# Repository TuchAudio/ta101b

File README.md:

# TuchAudio 101b
Discrete Phono preamp -- reedition of my very first phono preamp, circa 1987...

## Purpose
Fully symmetrical discrete op-amp phono preamp -- loosely inspirated by _Elektor_ designs. RIAA correction is achieved thru two different ways: low frequency boost is implemented on the feedback network, while the high-frequency rollof is done with a **passive low-pass filter**, for improved signal-to-noise ratio.

## Design quirks
The preamp itself is **fully DC-coupled**, for optimum bass performance; however, that means that the _input stage offset_ is **multiplied** by the low-frecuency gain (+34 dB), which may result on stage saturation. To compensate for that, each channel provides room for `R+` or `R-` resistors, connecting the inverting input (feedback) to the power rails, in case some manual adjustment is needed.

Just like the original build, a **subsonic filter** is integrated into the board. This is a **fourth-order high pass filter** (24 dB/oct) with a cutoff frequency of **11.8 Hz**; again, based on an _Elektor_ design (_Summer Circuits 1984_). However, since it is located _after_ the amplification, the high gain of the stage at low frequencies might saturate the preamp itself, in extreme cases.

DIN and RCA jacks are provided for signal input. Since the _native_ input impedance, being a symmetric op-amp design, is expected to be **extremely high**, space for suitable load (`Rx` and `Cx`) is provided for perfect adaptation; but for added flexibility, it is possible to use the free input for a suitable RC combo in parallel, to match the appropriate cartridge load.

Both direct and subsonic-filtered outputs are provided, and properly selected thru the [509 Input Selector board](../../../ta509). An aditional RCA **output** jack can be installed in order to use the circuit as a _stand-alone preamp_.

### Suggested mods

#### Subsonic output
As previously mentioned, both direct and subsonic outputs are provided, and selected thru the _509 Input Selector Board_; in case a non-selecting board is used (like the [501 Input Selector board](../../../ta501)), you can break the `JP1` and `JP2` jumpers to route the _subsonic_ output to the bus-style/RCA jack output instead (with suitable external bodge wires).

#### DC-block
While being fully DC-coupled is definitely desirable from a sound quality standpoint, it may be troublesome in some extreme cases, especially with _warped_ records. If this is a concern, adding a suitable _capacitor_ (**~100 µF**) in the feedback loop will prevent this. Just lift one pin of `R9/R109` and bodge the capacitor _in series_. **There is no need to use `R+/R-`** in that case, and you should remove them in order to check the _offset polarity_; mount the extra capacitor consequently.

## Specs

- **Power Supply:** +/- 9 V (symmetrical), just a few mA.
- **Gain at 1 kHz:** x50 (+34 dB)
- **Input sensitivity:** 3.6 mV (for 180 mV output)
- **Input impedance:** determined by `Rx/Cx`, either internal or external.
- **Output level and impedance:** 180 mV / 1 KΩ
- **Overload margin:** at least +15 dB
- **Signal-to-noise ratio:** more than 80 dB (estimated)
- **Distortion:** TBD

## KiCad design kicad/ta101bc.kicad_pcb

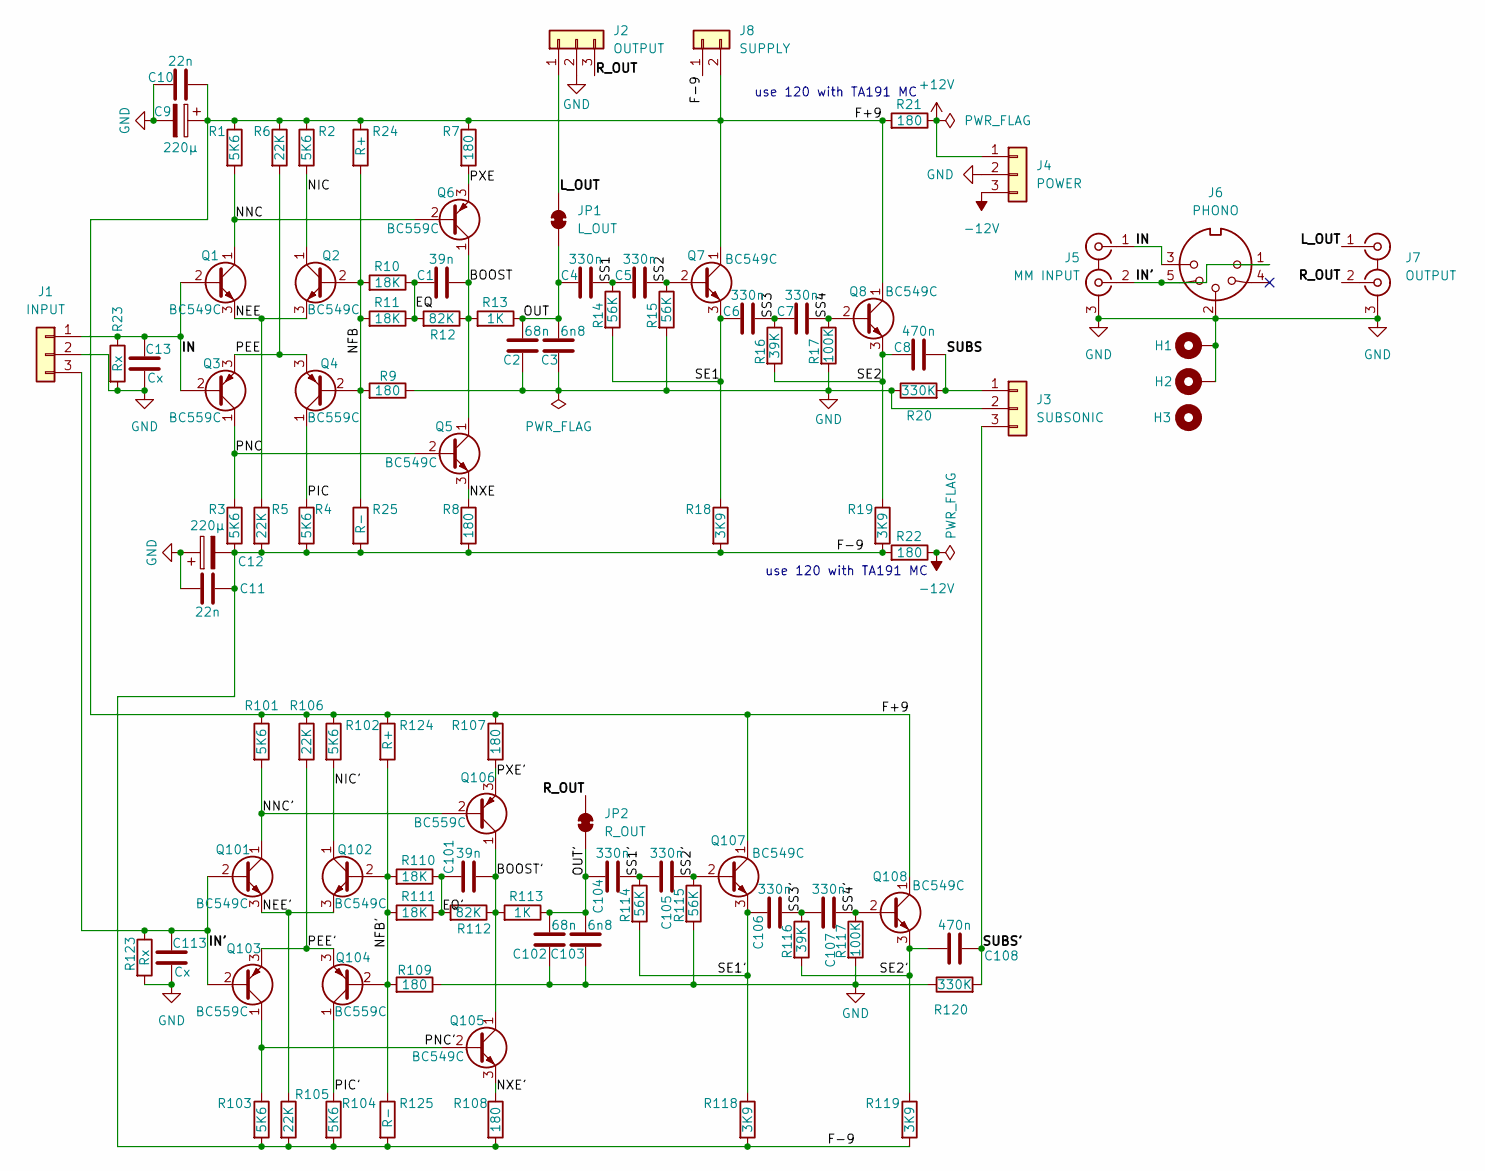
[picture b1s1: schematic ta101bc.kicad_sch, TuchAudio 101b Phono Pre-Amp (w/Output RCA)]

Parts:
C1, C101: 39n; C_Rect_L7.2mm_W3.0mm_P5.00mm_FKS2_FKP2_MKS2_MKP2
C2, C102: 68n; C_Rect_L7.2mm_W3.0mm_P5.00mm_FKS2_FKP2_MKS2_MKP2
C3, C103: 6n8; C_Rect_L7.2mm_W3.0mm_P5.00mm_FKS2_FKP2_MKS2_MKP2
C4, C5, C6, C7, C104, C105, C106, C107: 330n; C_Rect_L7.2mm_W3.0mm_P5.00mm_FKS2_FKP2_MKS2_MKP2
C8, C108: 470n; C_Rect_L7.2mm_W3.0mm_P5.00mm_FKS2_FKP2_MKS2_MKP2
C9, C12: 220µ; CP_Radial_D6.3mm_P2.50mm
C10, C11: 22n; C_Disc_D6.0mm_W2.5mm_P5.00mm
C13, C113: Cx; PinSocket_1x02_P2.54mm_Vertical
H1, H2: MountingHole_Pad; MountingHole_3.2mm_M3_DIN965_Pad
H3: MountingHole; MountingHole_3.2mm_M3_DIN965
J1: INPUT; PinHeader_1x03_P2.54mm_Vertical
J2: OUTPUT; PinHeader_1x03_P2.54mm_Vertical
J3: SUBSONIC; PinHeader_1x03_P2.54mm_Vertical
J4: POWER; PinHeader_1x03_P2.54mm_Vertical
J5: MM INPUT; 2xRCA_vertical
J6: PHONO; DIN 5-180deg
J7: OUTPUT; 2xRCA_vertical
J8: SUPPLY; PinHeader_1x02_P2.54mm_Vertical
JP1: L_OUT; SolderJumper-2_P1.3mm_Bridged2Bar_RoundedPad1.0x1.5mm
JP2: R_OUT; SolderJumper-2_P1.3mm_Bridged2Bar_RoundedPad1.0x1.5mm
Q1, Q2, Q5, Q7, Q8, Q101, Q102, Q105, Q107, Q108: BC549C; TO-92_Inline
Q3, Q4, Q6, Q103, Q104, Q106: BC559C; TO-92_Inline
R1, R2, R3, R4, R101, R102, R103, R104: 5K6; R_Axial_DIN0207_L6.3mm_D2.5mm_P10.16mm_Horizontal
R5, R6, R105, R106: 22K; R_Axial_DIN0207_L6.3mm_D2.5mm_P10.16mm_Horizontal
R7, R8, R9, R21, R22, R107, R108, R109: 180; R_Axial_DIN0207_L6.3mm_D2.5mm_P10.16mm_Horizontal
R10, R11, R110, R111: 18K; R_Axial_DIN0207_L6.3mm_D2.5mm_P10.16mm_Horizontal
R12, R112: 82K; R_Axial_DIN0207_L6.3mm_D2.5mm_P10.16mm_Horizontal
R13, R113: 1K; R_Axial_DIN0207_L6.3mm_D2.5mm_P10.16mm_Horizontal
R14, R15, R114, R115: 56K; R_Axial_DIN0207_L6.3mm_D2.5mm_P10.16mm_Horizontal
R16, R116: 39K; R_Axial_DIN0207_L6.3mm_D2.5mm_P10.16mm_Horizontal
R17, R117: 100K; R_Axial_DIN0207_L6.3mm_D2.5mm_P10.16mm_Horizontal
R18, R19, R118, R119: 3K9; R_Axial_DIN0207_L6.3mm_D2.5mm_P10.16mm_Horizontal
R20, R120: 330K; R_Axial_DIN0207_L6.3mm_D2.5mm_P10.16mm_Horizontal
R23, R123: Rx; PinSocket_1x02_P2.54mm_Vertical
R24, R124: R+; PinSocket_1x02_P2.54mm_Vertical
R25, R125: R-; PinSocket_1x02_P2.54mm_Vertical

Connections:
+12V: J4.1, R21.1
-12V: J4.3, R22.1
/BOOST: C1.2, Q5.1 (C), Q6.1 (C), R12.1, R13.2
/BOOST': C101.2, Q105.1 (C), Q106.1 (C), R112.1, R113.2
/EQ: C1.1, R10.1, R11.1, R12.2
/EQ': C101.1, R110.1, R111.1, R112.2
/F+9: C9.1, C10.2, J8.2, Q7.1 (C), Q8.1 (C), Q107.1 (C), Q108.1 (C), R1.1, R2.1, R6.1, R7.1, R21.2, R24.1, R101.1, R102.1, R106.1, R107.1, R124.1
/F-9: C11.2, C12.2, J8.1, R3.2, R4.2, R5.2, R8.2, R18.2, R19.2, R22.2, R25.2, R103.2, R104.2, R105.2, R108.2, R118.2, R119.2, R125.2
/IN: C13.1, J1.1, J5.1 (IN1), J6.3, Q1.2 (B), Q3.2 (B), R23.1
/IN': C113.1, J1.3, J5.2 (IN2), J6.1, J6.5, Q101.2 (B), Q103.2 (B), R123.1
/L_OUT: J2.1, J7.1 (IN1), JP1.2 (B)
/NEE: Q1.3 (E), Q2.3 (E), R5.1
/NEE': Q101.3 (E), Q102.3 (E), R105.1
/NFB: Q2.2 (B), Q4.2 (B), R9.2, R10.2, R11.2, R24.2, R25.1
/NFB': Q102.2 (B), Q104.2 (B), R109.2, R110.2, R111.2, R124.2, R125.1
/NIC: Q2.1 (C), R2.2
/NIC': Q102.1 (C), R102.2
/NNC: Q1.1 (C), Q6.2 (B), R1.2
/NNC': Q101.1 (C), Q106.2 (B), R101.2
/NXE: Q5.3 (E), R8.1
/NXE': Q105.3 (E), R108.1
/OUT: C2.1, C3.1, C4.1, JP1.1 (A), R13.1
/OUT': C102.1, C103.1, C104.1, JP2.1 (A), R113.1
/PEE: Q3.3 (E), Q4.3 (E), R6.2
/PEE': Q103.3 (E), Q104.3 (E), R106.2
/PIC: Q4.1 (C), R4.1
/PIC': Q104.1 (C), R104.1
/PNC: Q3.1 (C), Q5.2 (B), R3.1
/PNC': Q103.1 (C), Q105.2 (B), R103.1
/PXE: Q6.3 (E), R7.2
/PXE': Q106.3 (E), R107.2
/R_OUT: J2.3, J7.2 (IN2), JP2.2 (B)
/SE1: C6.1, Q7.3 (E), R14.2, R18.1
/SE1': C106.1, Q107.3 (E), R114.2, R118.1
/SE2: C8.1, Q8.3 (E), R16.2, R19.1
/SE2': C108.1, Q108.3 (E), R116.2, R119.1
/SS1: C4.2, C5.1, R14.1
/SS1': C104.2, C105.1, R114.1
/SS2: C5.2, Q7.2 (B), R15.1
/SS2': C105.2, Q107.2 (B), R115.1
/SS3: C6.2, C7.1, R16.1
/SS3': C106.2, C107.1, R116.1
/SS4: C7.2, Q8.2 (B), R17.1
/SS4': C107.2, Q108.2 (B), R117.1
/SUBS: C8.2, J3.1, R20.2
/SUBS': C108.2, J3.3, R120.2
GND: C2.2, C3.2, C9.2, C10.1, C11.1, C12.1, C13.2, C102.2, C103.2, C113.2, H1.1, H2.1, J1.2, J2.2, J3.2, J4.2, J5.3 (EXT), J6.2, J7.3 (EXT), R9.1, R15.2, R17.2, R20.1, R23.2, R109.1, R115.2, R117.2, R120.1, R123.2

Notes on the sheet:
use 120 with TA191 MC

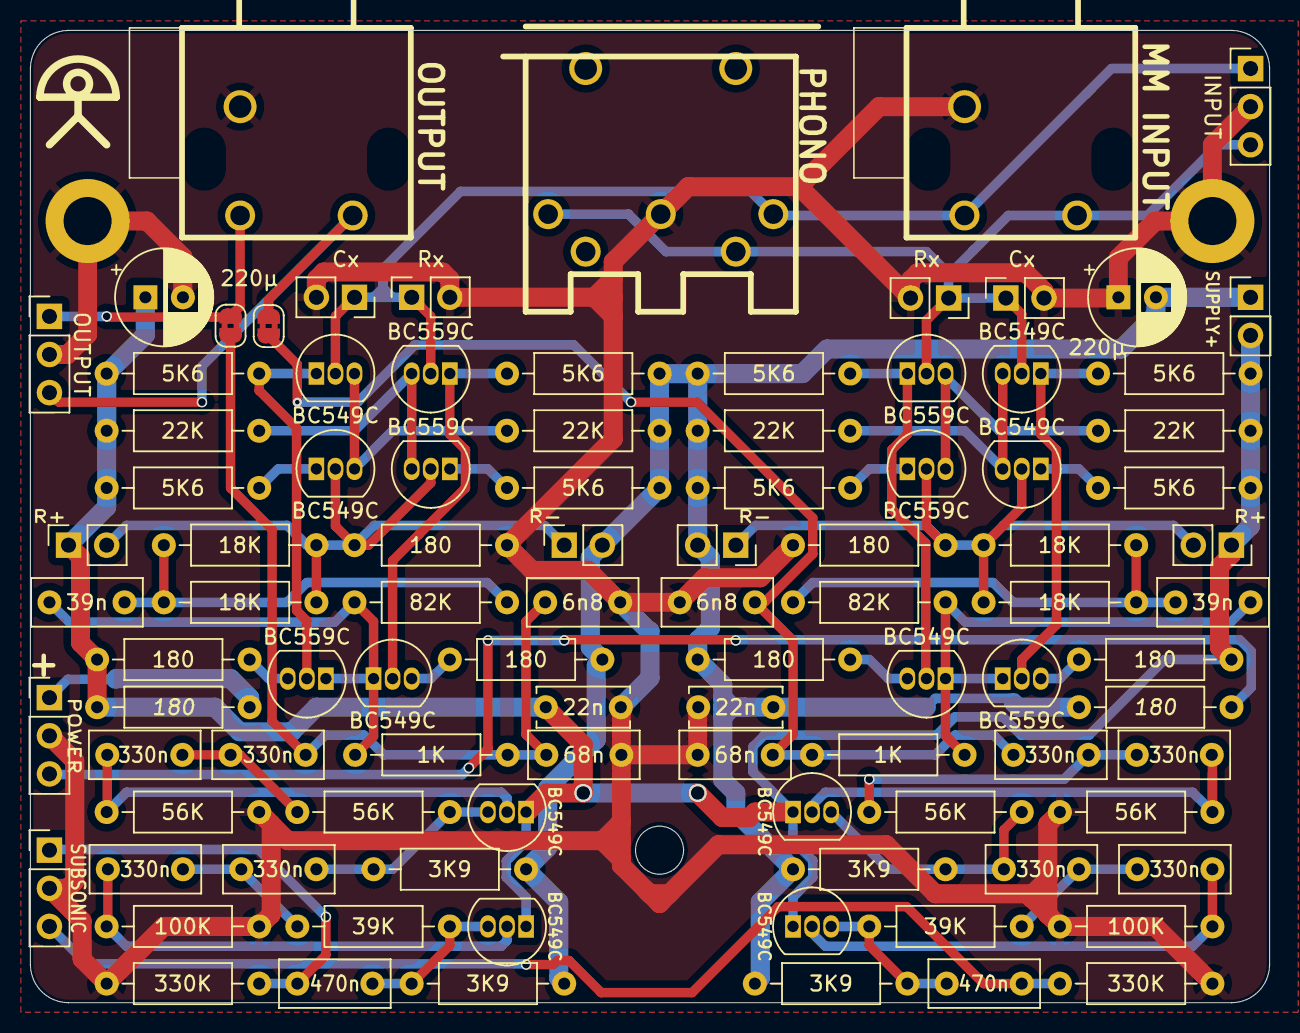
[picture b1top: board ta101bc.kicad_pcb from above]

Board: 2 copper layers, 82.6 x 64.8 mm, 99 parts (0 on the bottom side), 47 nets.

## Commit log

2025-11-08 add KiCAD files
2025-11-12 Power supply requeriments
2025-11-12 add pictures
2025-11-24 add links
2025-11-29 fix form factor
2026-01-16 MC resistor option, improve silkscreen
